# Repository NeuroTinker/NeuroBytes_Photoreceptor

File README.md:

# NeuroBytes Rod Photoreceptor

The NeuroBytes Rod Photoreceptor is an open-source hardware neuron simulator designed and sold by [NeuroTinker, LLC](http://www.neurotinker.com/). 

All NeuroBytes products are based on the ST32L0x series of ARM Cortex-M0+ 32-bit microcontrollers. The boards were designed in KiCad and Inkscape and are released under the terms of the Creative Commons Attribution-ShareAlike 4.0 license, available here: http://creativecommons.org/licenses/by-sa/4.0/. The NeuroBytes Rod Photoreceptor is Certified Open Source Hardware as defined by [OSHWA](https://www.oshwa.org), certification number US000108.

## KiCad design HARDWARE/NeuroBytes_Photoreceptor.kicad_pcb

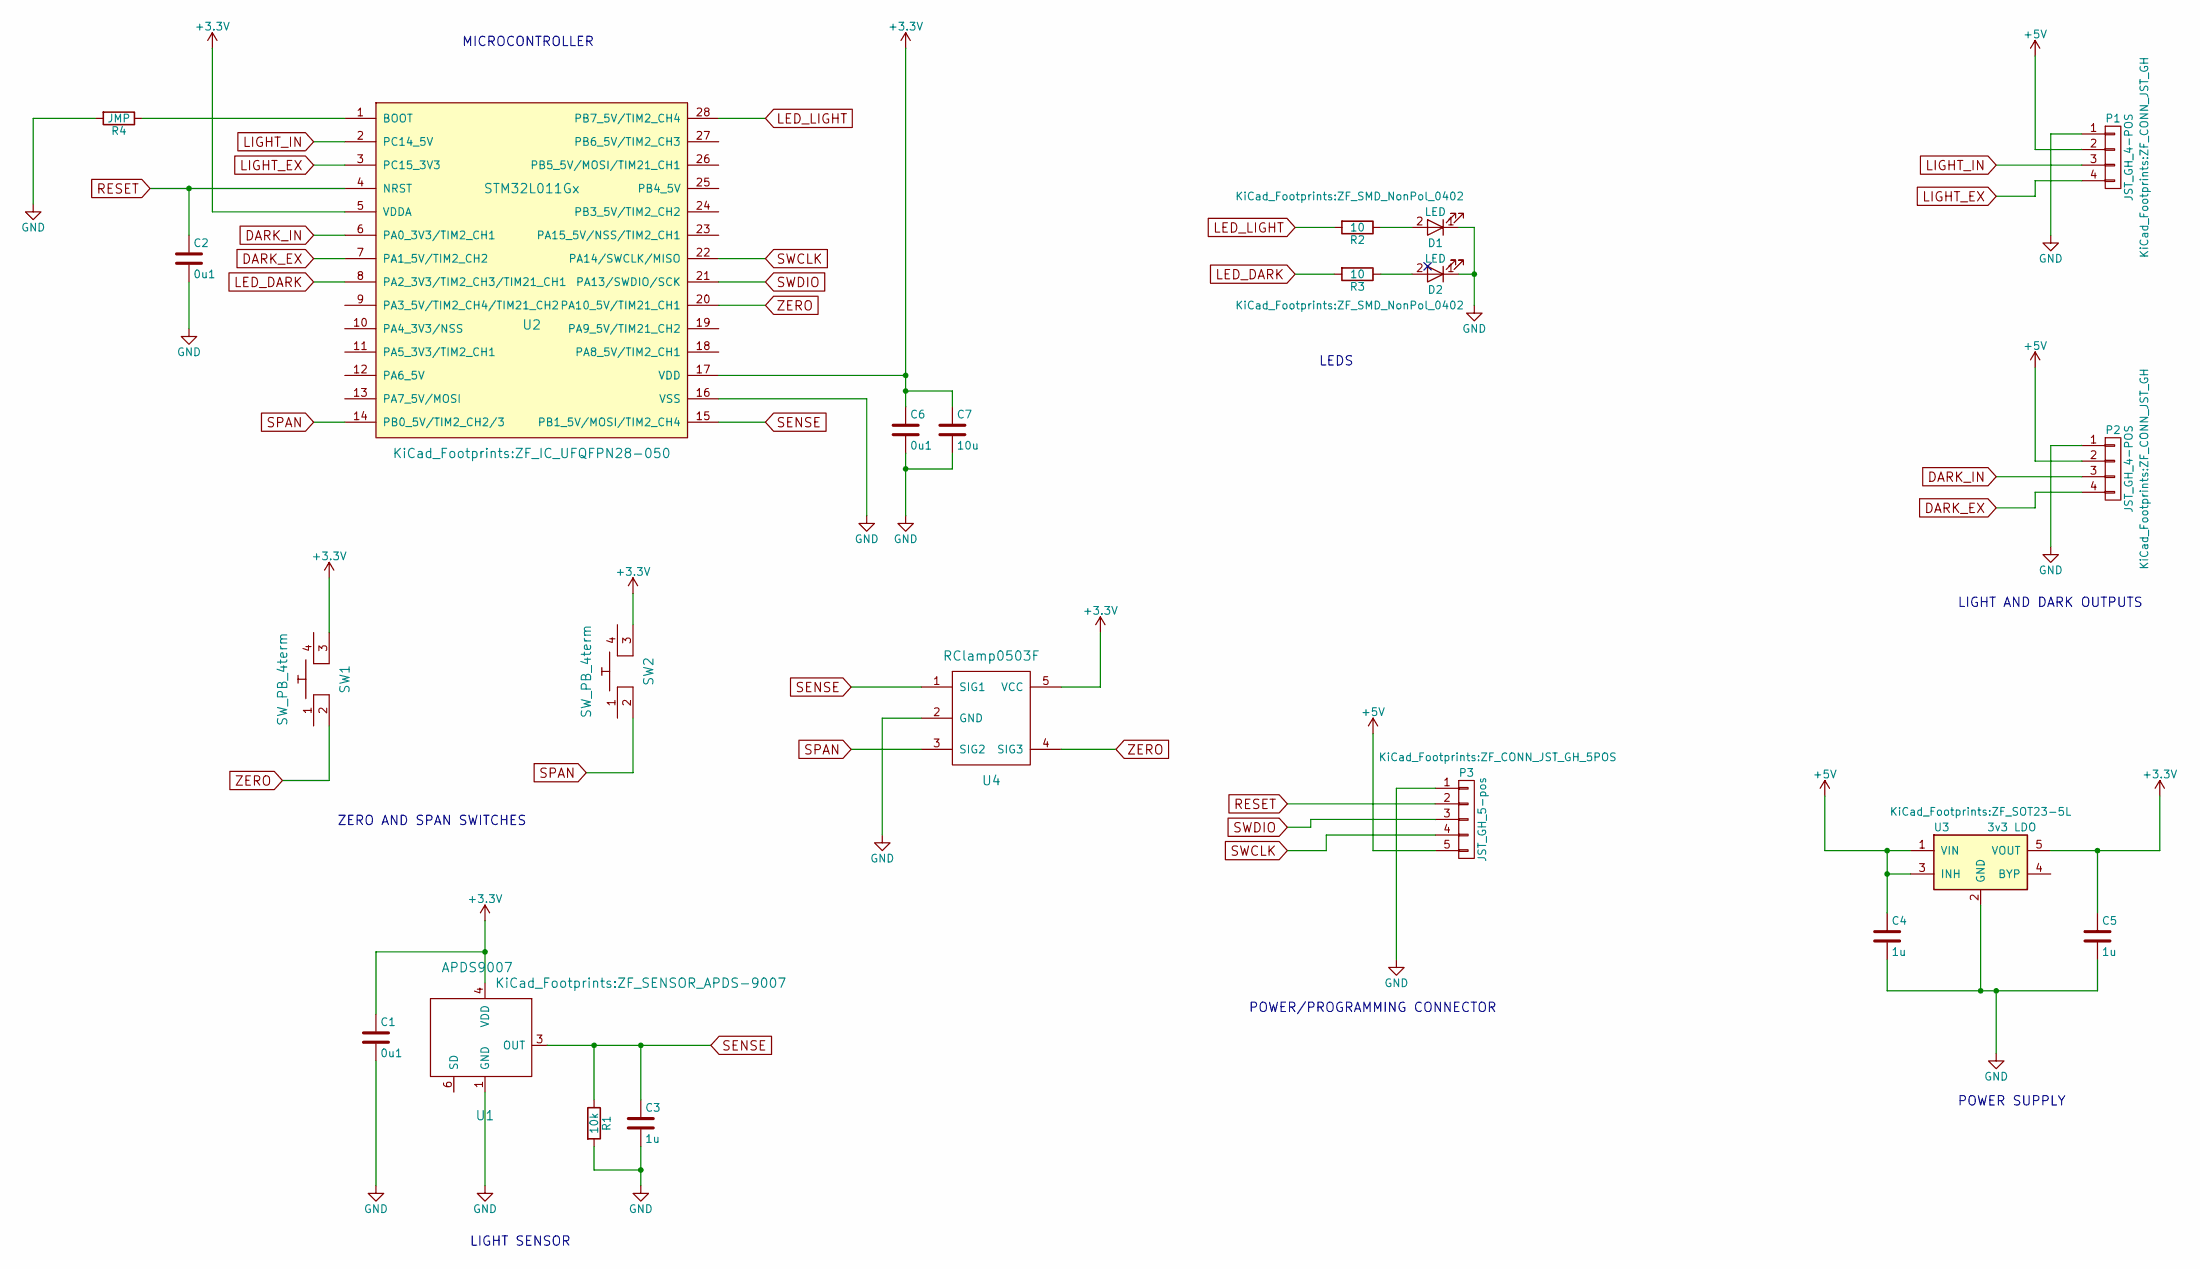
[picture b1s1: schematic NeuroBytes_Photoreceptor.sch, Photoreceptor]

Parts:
C1, C2, C6: 0u1; ZF_SMD_NonPol_0402_cap; Mfr Part # LMK105BJ104KV-F
C3, C4, C5: 1u; C_0603_HandSoldering; Mfr Part # LMK107B7105KA-T
C7: 10u; C_1206; Mfr Part # EMK316B7106KL-TD
D1, D2: LED; ZF_SMD_NonPol_0402; Mfr Part # SCMP13WBC8W1
P1, P2: JST_GH_4-POS; ZF_CONN_JST_GH; Mfr Part # SM04B-GHS-TB(LF)(SN)
P3: JST_GH_5-pos; ZF_CONN_JST_GH_5POS; Mfr Part # SM05B-GHS-TB(LF)(SN)
R1: 10k; ZF_SMD_NonPol_0402; Mfr Part # RC0402FR-0710KL
R2, R3: 10; ZF_SMD_NonPol_0402; Mfr Part # RC0402FR-0710RL
R4: JMP; ZF_SMD_NonPol_0402; Mfr Part # RC0402JR-070RL
SW1, SW2: SW_PB_4term; ZF_SW_PTS810; Mfr Part # PTS810 SJM 250 SMTR LFS
U1: APDS9007; ZF_SENSOR_APDS-9007; Mfr Part # APDS-9007-020
U2: STM32L011Gx; ZF_IC_UFQFPN28-050; Mfr Part # STM32L011G4U6
U3: 3v3 LDO; ZF_SOT23-5L; Mfr Part # NCP114BSN330T1G
U4: RClamp0503F; ZF_SMD_SOT-353; Mfr Part # RCLAMP0503F.TCT

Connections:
+3V3: C1.1, C5.1, C6.1, C7.1, SW1.3, SW2.3, U1.4 (VDD), U2.5 (VDDA), U2.17 (VDD), U3.5 (VOUT), U4.5 (VCC)
+5V: C4.1, P1.2, P2.2, P3.5, U3.1 (VIN), U3.3 (INH)
DARK_EX: P2.4, U2.7 (PA1_5V/TIM2_CH2)
DARK_IN: P2.3, U2.6 (PA0_3V3/TIM2_CH1)
GND: C1.2, C2.2, C3.2, C4.2, C5.2, C6.2, C7.2, D1.1 (K), D2.1 (K), P1.1, P2.1, P3.1, R1.2, R4.2, U1.1 (GND), U2.16 (VSS), U3.2 (GND), U4.2 (GND)
LED_DARK: R3.2, U2.8 (PA2_3V3/TIM2_CH3/TIM21_CH1)
LED_LIGHT: R2.2, U2.28 (PB7_5V/TIM2_CH4)
LIGHT_EX: P1.4, U2.3 (PC15_3V3)
LIGHT_IN: P1.3, U2.2 (PC14_5V)
unnamed: D1.2 (A), R2.1
unnamed: D2.2 (A), R3.1
unnamed: R4.1, U2.1 (BOOT)
RESET: C2.1, P3.2, U2.4 (NRST)
SENSE: C3.1, R1.1, U1.3 (OUT), U2.15 (PB1_5V/MOSI/TIM2_CH4), U4.1 (SIG1)
SPAN: SW2.2, U2.14 (PB0_5V/TIM2_CH2/3), U4.3 (SIG2)
SWCLK: P3.4, U2.22 (PA14/SWCLK/MISO)
SWDIO: P3.3, U2.21 (PA13/SWDIO/SCK)
ZERO: SW1.2, U2.20 (PA10_5V/TIM21_CH1), U4.4 (SIG3)

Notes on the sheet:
MICROCONTROLLER
ZERO AND SPAN SWITCHES
LIGHT SENSOR
POWER/PROGRAMMING CONNECTOR
LEDS
POWER SUPPLY
LIGHT AND DARK OUTPUTS

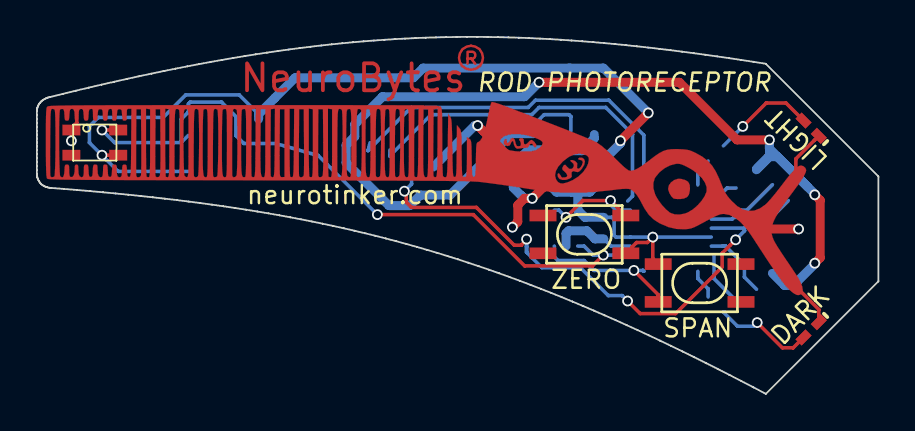
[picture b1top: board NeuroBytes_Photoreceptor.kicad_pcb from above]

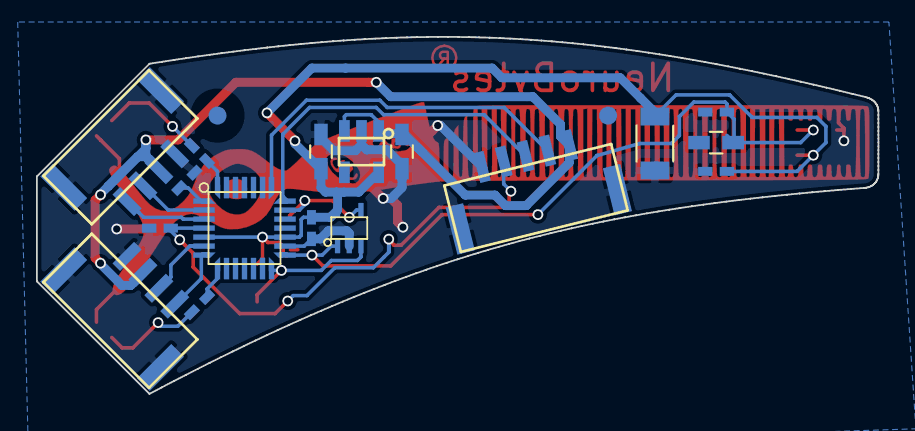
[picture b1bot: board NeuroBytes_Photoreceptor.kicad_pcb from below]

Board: 2 copper layers, 46.8 x 19.8 mm, 22 parts (17 on the bottom side), 18 nets.

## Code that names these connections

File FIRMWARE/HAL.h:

#ifndef HAL_H_
#define HAL_H_

#include <libopencm3/stm32/rcc.h>
#include <libopencm3/stm32/gpio.h>
#include <libopencm3/stm32/timer.h>
#include <libopencm3/cm3/nvic.h>
#include <libopencm3/cm3/systick.h>
#include <libopencm3/stm32/exti.h>
#include <libopencm3/stm32/adc.h>


#include "comm.h"

#define PORT_LED_LIGHT	GPIOB
#define PIN_LED_LIGHT	GPIO7

#define PORT_LED_DARK	GPIOA
#define PIN_LED_DARK	GPIO2

#define PORT_LIGHT_OUT	GPIOC
#define PIN_LIGHT_EX	GPIO15
#define PIN_LIGHT_IN	GPIO14

#define PORT_DARK_OUT	GPIOA
#define PIN_DARK_EX	    GPIO1
#define PIN_DARK_IN	    GPIO0

#define PORT_SPAN		GPIOB
#define PIN_SPAN		GPIO0

#define PORT_ZERO		GPIOA
#define PIN_ZERO		GPIO10

#define PORT_SENSE		GPIOB
#define PIN_SENSE		GPIO1

extern volatile uint8_t tick;
extern volatile uint8_t main_tick;

void systick_setup(int freq);
void clock_setup(void);
void gpio_setup(void);
void tim_setup(void);
void adc_setup(void);
void setLED(uint8_t led, uint16_t val);
void setAsInput(uint32_t port, uint32_t pin);
void setAsOutput(uint32_t port, uint32_t pin);
uint8_t readButton(uint8_t button);

#endif

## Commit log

2017-03-23 Added first hardware files (PCB, schematic, graphics). Two versions on layout, stubby and regular. Note that BOOT0 isn't connected to GND, so it must be bodged!
2017-03-23 added libopencm3 as submodule
2017-03-24 Demo code to test the ADC, zero/span functionality, and general light sensor characteristics. LEDs fade (PWM via TIM2) inversely based on ambient light.
2017-05-10 Iterated hardware design to incorporate several new features: (1) PCB outline no longer in line with cell wall; rather, entire photoreceptor is displayed on front in copper, and PCB outline is design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
2017-05-10 Moved SENSE line from PB6 to PB1 so it's now on an ADC line (ADC9). Bodging prototypes.
2017-05-10 Reloaded ground pour to take moved SENSE line into account.
2017-05-11 Updated HAL.c and HAL.h to reflect new firmware.
2017-05-15 added schematic library submodule
2017-05-15 Updated KiCad project file to reference library submodule
2017-05-16 Updated Gerber files. Added BOM. Added component values to schematic. Added fiducials.
2017-05-19 updating submodules
2017-05-19 Update submodules and .gitmodules file
2017-05-19 make clean
2017-05-31 Updated swith footprint.
2017-05-31 Another switch footprint update
2017-05-31 minor PCB updates to improve manufacturability (sp?)
2017-07-04 tweaked parameters
2017-07-25 added .gitignore
2017-07-25 added fingerprint
2017-08-10 added .fingerprint
2017-08-11 updated fingerprint
2017-08-11 Changed to 5-pin JST GH connector for programming and power. Added POWER label. Minor routing changes.
2017-08-11 add fingerprint
2017-08-11 changed fingerprint address
2017-08-28 added kicad fonts to *.svg. exported board render.
2017-09-06 illustration update
2017-09-06 new *.png exports
2017-09-07 added picture to readme.md
2017-09-11 fixed simultaneous excitation issue
2017-09-11 made elf
2017-09-22 deleted flash.gdb from FIRMWARE directory. added photoreceptor board export.
2017-09-22 regenerated and loaded netlist. deleted old Gerbers and other misc files.
2017-09-22 updated component descriptions. reloaded netlist. minor PCB updates. fresh *.csv export.
2017-10-03 minor page layout updates
2017-11-01 demo build
2017-11-02 switched to systick and fixed stalling
2017-11-30 updated license, readme, and PCB. CC-BY-SA 4.0
2018-01-30 prep for merge. made elf.
2018-01-30 resolve merge conflicts
2018-02-13 schematic library update
2018-02-13 added ESD protection. updated title block. minor routing changes.
2018-03-08 added OSHWA cert logo to README.md
2018-05-23 generated fab files. generated BOM.
2018-05-31 exported schematic *.pdf
2018-08-06 updated footprints to include B.Fab outlines. minor routing changes. re-generated Gerbers. added placement pdf.
2018-08-08 regen drill file
2018-12-29 fix zero/span overlap

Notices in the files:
HARDWARE/NeuroBytes_Photoreceptor.kicad_pcb:
(C) 2017 Zach Fredin
License: CC-BY-SA 4.0
HARDWARE/NeuroBytes_Photoreceptor.sch:
(C) 2018 Zach Fredin
